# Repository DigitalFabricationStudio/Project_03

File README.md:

Project_03
==========

The projects developed during the Digital Fabrication Studio course, 0.2 edition

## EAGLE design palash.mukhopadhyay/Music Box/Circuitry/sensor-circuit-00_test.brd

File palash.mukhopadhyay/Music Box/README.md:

MusicBox
============

Making a hand-cranked music box that converts images into sound.

More detailed write-up soon.

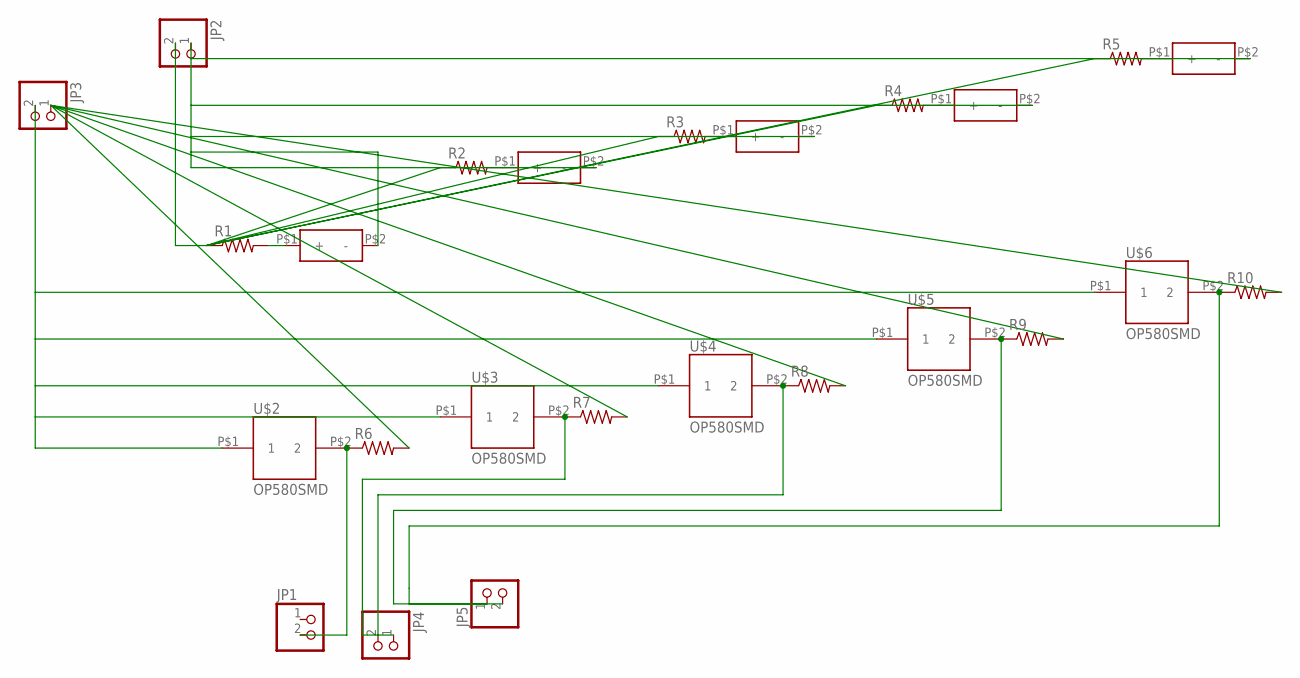
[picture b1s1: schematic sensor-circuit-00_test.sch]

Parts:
JP1, JP2, JP3, JP4, JP5: PINHD-1X2; 1X02
R1, R2, R3, R4, R5, R6, R7, R8, R9, R10: RESISTOR1206; 1206
U$1, U$7, U$8, U$9, U$10: OP280SMD; OP280
U$2, U$3, U$4, U$5, U$6: OP580SMD; OP580

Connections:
unnamed: R1.2, U$1.P$1 (+)
unnamed: R2.2, U$7.P$1 (+)
unnamed: R3.2, U$8.P$1 (+)
unnamed: R4.2, U$9.P$1 (+)
unnamed: R5.2, U$10.P$1 (+)
unnamed: JP1.2, R6.1, U$2.P$2 (2)
unnamed: JP4.2, R7.1, U$3.P$2 (2)
unnamed: JP4.1, R8.1, U$4.P$2 (2)
unnamed: JP5.2, R9.1, U$5.P$2 (2)
unnamed: JP5.1, R10.1, U$6.P$2 (2)
unnamed: JP3.2, U$2.P$1 (1), U$3.P$1 (1), U$4.P$1 (1), U$5.P$1 (1), U$6.P$1 (1)
unnamed: JP3.1, R6.2, R7.2, R8.2, R9.2, R10.2
unnamed: JP2.1, U$1.P$2 (-), U$7.P$2 (-), U$8.P$2 (-), U$9.P$2 (-), U$10.P$2 (-)
unnamed: JP2.2, R1.1, R2.1, R3.1, R4.1, R5.1

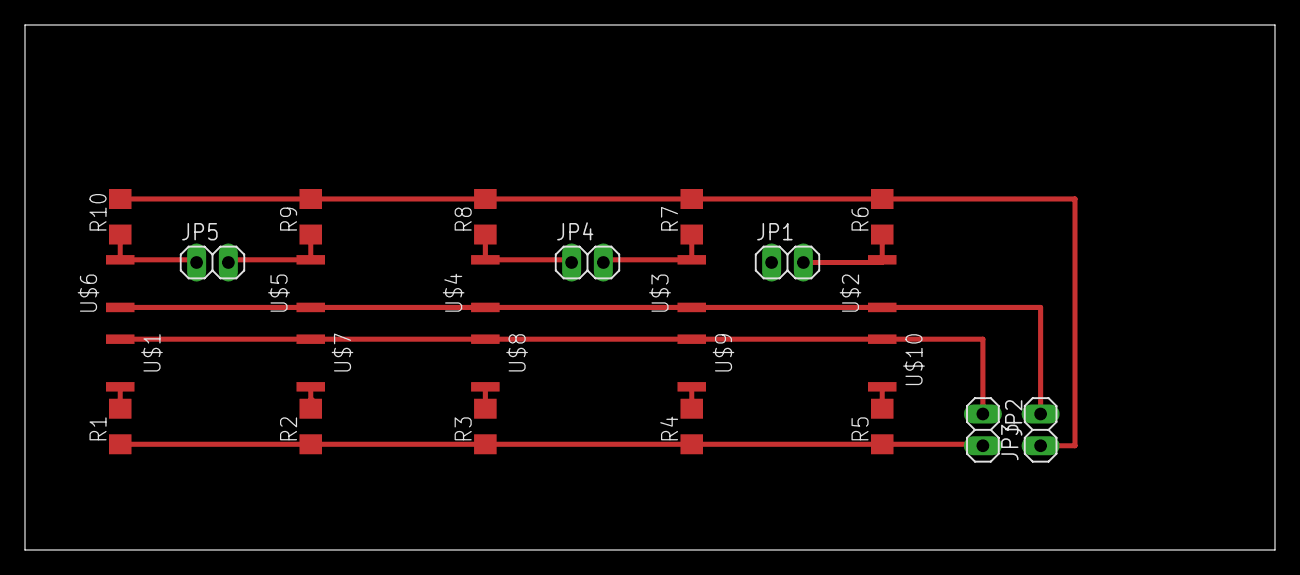
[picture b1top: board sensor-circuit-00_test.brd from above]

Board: 2 copper layers, 100.0 x 42.0 mm, 25 parts (0 on the bottom side), 14 nets.

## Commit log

2013-05-03 Antti Hietaniemi bio added
2013-05-03 adding folder
2013-05-03 moved bio md to folder
2013-05-03 added folder
2013-05-03 Yunhye Kim
2013-05-03 eugenia.pavone
2013-05-03 corrected folder name
2013-05-03 my folder
2013-05-06 box project folder added
2013-05-06 add olli.romppanen bio
2013-05-06 updating bio
2013-05-06 Adding a short bio for palash
2013-05-06 add folder for lasercutting projects
2013-05-06 add final file and picture of the box
2013-05-06 added box pdf
2013-05-06 added desc
2013-05-06 add less loose box
2013-05-06 ah_box.jpg added
2013-05-06 smaller pic size
2013-05-08 3D model of palash
2013-05-08 add 3d project folder
2013-05-08 try commit
2013-05-08 another try update
2013-05-10 Lasercut box
2013-05-10 remove DS_Store
2013-05-10 remove .DS_Store
2013-05-10 Better names
2013-05-10 add cast model for CNC drilling
2013-05-10 add cast model files
2013-05-13 renamed Yunhye.Kim.md.txt to .md only
2013-05-13 Add all the files so far
2013-05-13 fix error
2013-05-13 the latest file for milling (cleaned one)
2013-05-13 add laser cut folder
2013-05-13 add 3D print folder
2013-05-13 add milling folder
2013-05-14 create bio file
2013-05-14 add bio and user file image
2013-05-14 update bio
2013-05-14 added lasercut and 3D files
2013-05-14 add milling pics
2013-05-14 update laser cutter files
2013-05-14 update box pics
2013-05-14 add 123D catch .stl file
2013-05-14 add 3D_head model
2013-05-14 add readme.md for 3D printing
2013-05-14 add pic readme.md_3D printing
2013-05-14 add readme.md for milling
2013-05-14 add img source
2013-05-14 update img src
2013-05-14 add 3D_head pic to readme.md
2013-05-14 add txt file to laser cutter folder
2013-05-14 update readme.md for laser cut
2013-05-14 box lasercut update
2013-05-14 .DS_Store
2013-05-15 add molding folder
2013-05-15 add pics mold
2013-05-15 add antti scan
2013-05-15 add .gitignore for .DS_Store
2013-05-15 rm .DS_Store
2013-05-15 3d model and a mold
2013-05-15 laser cut folder update
2013-05-16 added pic
2013-05-16 stl model on back and 3d print
2013-05-20 Adding the CAM files for the first test of Tatiana's final project
2013-05-20 add final project folder
2013-05-20 add milling board 3dm
2013-05-20 add x&o laser file
2013-05-20 add box living hinge laser file
2013-05-21 add folder for brass instrument mute project
2013-05-21 Add second day of milling of Tania table
2013-05-21 add file for cnc milling
2013-05-21 add stl file for brass mute
2013-05-21 add images of the air filter part of the mute
2013-05-21 add image of the silicon cast
2013-05-21 add packaging template
2013-05-21 update laser file
2013-05-21 add milling 3dm
2013-05-21 add milling files for final project
2013-05-21 update files for final project
2013-05-21 update molding file
2013-05-21 add files for final project
2013-05-22 creating readme file for the final project
2013-05-22 add description of the project
2013-05-22 add future developments of the project to the readme
2013-05-22 add image of failed efforts to print real size mute with various settings
2013-05-22 add image of mute parts
2013-05-22 update laser cut files for final project
2013-05-22 update package file_final project
2013-05-22 renaming files & add pictures
2013-05-23 Lasercutting and 3D cleaning
2013-05-23 3D Printing and Milling added
2013-05-23 Updating .md files
2013-05-23 Updating profile readme
2013-05-23 Adding Music Box and Eagle files
2013-05-23 all the files and project
2013-05-23 add project images
2013-05-23 add final presentation PD file
2013-05-23 Final cutting file
2013-05-23 add photos
2013-05-23 reupload molding and casting and final project
2013-05-23 presentation
2013-05-23 Presentation and CC license
2013-05-23 Updated presentation
2013-05-23 add final presentation
2013-05-23 update laser package
2013-05-23 add final prototype shots
2013-05-23 add testing shots
2013-05-23 add readme file to final project
2013-05-23 Arduino source-code
2013-05-23 add cc
2013-05-26 update readme final project
2013-05-26 update readme_final project
2013-05-26 add laser files
2013-05-26 add jpeg laser files
2013-05-27 add another failed mute print image
2013-06-18 Adding Martin final presentation
2013-06-24 Add Martin exercise
